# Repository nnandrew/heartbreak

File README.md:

# heartbreak
a 40 Key Wireless BLE Split Keyboard with Encoders, LCDs, Haptic Feedback, Fingerprint Reading, Underglow, and a corny theme.

## Parts
### Required

| Name | Count | Notes |
|:-|:-|:-|
| PCB | 2 | Reversible |
| PCB Coin | 1-2 | fills case hole with a <3 |
| Top Shell | 2  | 3D printed or machined integrated plate |
| Bottom Shell | 2  | Transparent resin print |
| Magnets | 48  | 3x1mm to hold the case together |
| nice!nano v2.0 | 2 | ZMK BLE |
| MCU Sockets | 50-70 | 0627-0-15-15-21-27-10-0 | 
| MCU Pins | 50-70 | 3320-0-00-15-00-00-03-0 |
| Reset Switch | 2 | B3U-3000P-B |
| Power Switch | 2 | PCM12 |
| Battery | 2 | 301230 size |
| Diodes | 42 | SOD-123 SMD |
| Switch Sockets | 40 | Kailh sockets |
| Key Switches | 40 | Only compatible with MX style |
| Keycaps | 40 | All 1u |
| USB C cable | 1 | Data lines required for flashing |

### Optional

| Name | Count | Remarks |
|:-|:-|:-|
| Rubber feet | 8 | reduce sliding |
| nice!view LCD | 2 | low power draw |
| Pimoroni Haptic Buzz | 1 | requires custom firmware |
| Waveshare UART Fingerprint Sensor | 1 | requires custom firmware |
| EC11 Rotary Encoder | 2 | using hardware debouncing |
| 17mm Encoder Knob | 2 | a tight fit |
| Schmitt Trigger | 2 | 74AUP2G14 |
| 10kOhm Resistors | 8 | encoder debounce |
| 0.1uC Capacitors | 4 | for leds and debounce |
| WS2812B | 9 | LEDs for Undergrow |
| SK6812-SIDE | 4 | LEDs for Undergrow |
| P-Channel MOSFET | 2 | SOT-23 to shutoff LEDs |
| 200Ohm Resistors | 2 | current limit for mosfet |
| 200kOhm Resistors | 2 | pulldown for mosfet |
| 0.1uC Capacitors | 26 | for leds and debounce |

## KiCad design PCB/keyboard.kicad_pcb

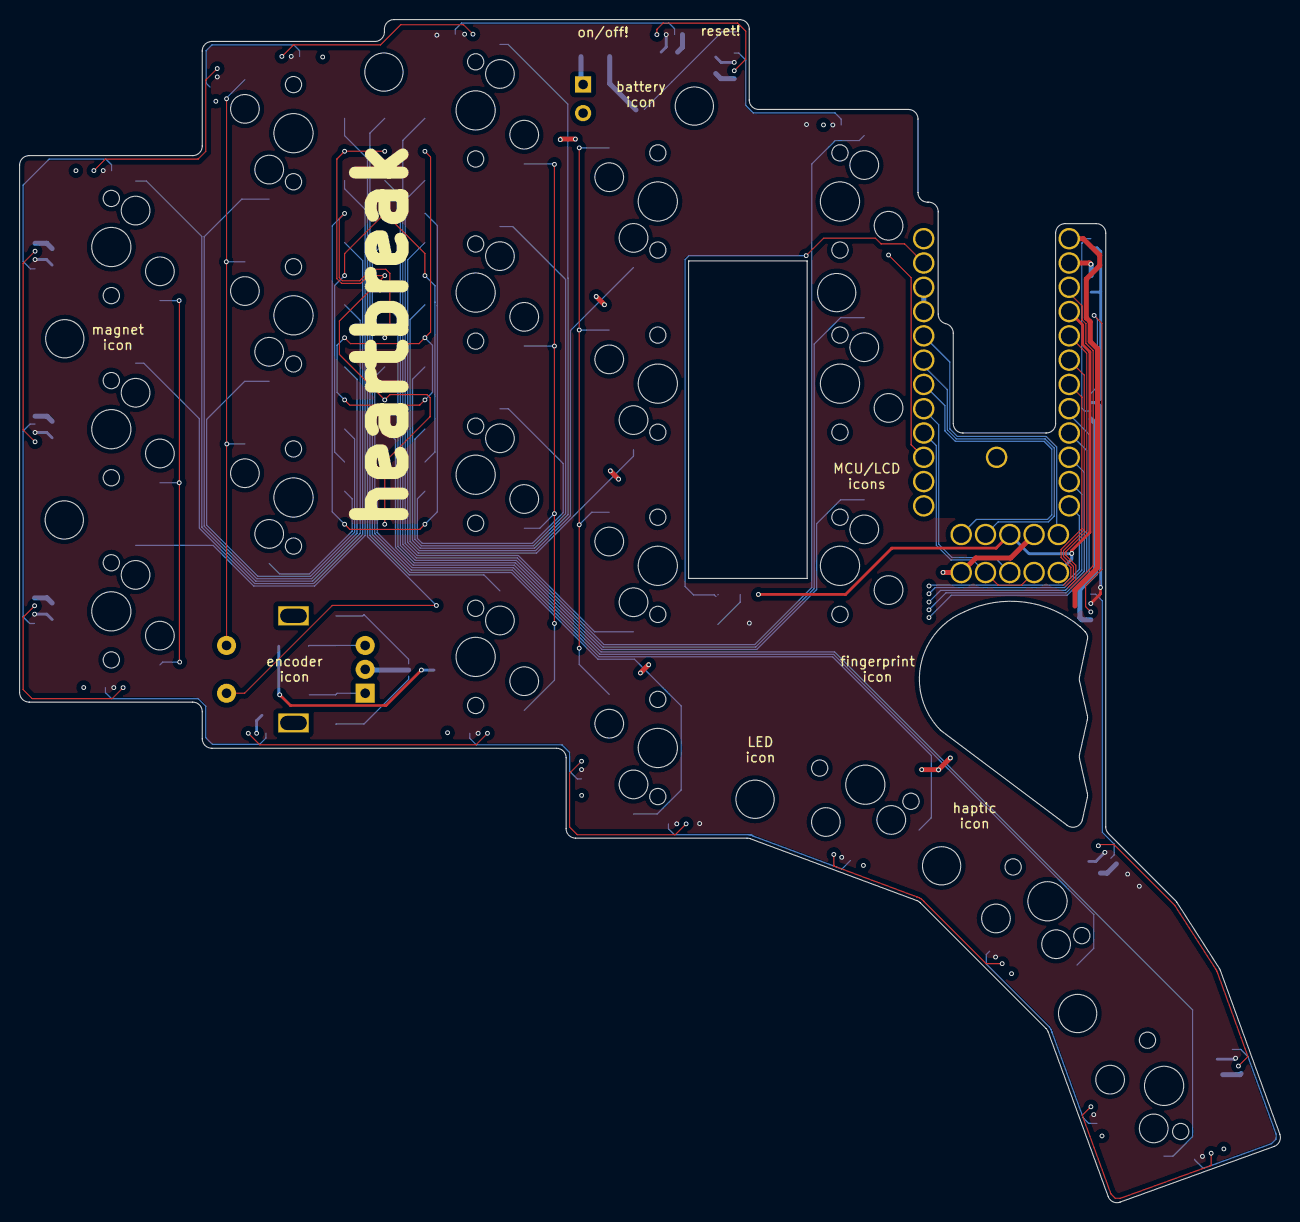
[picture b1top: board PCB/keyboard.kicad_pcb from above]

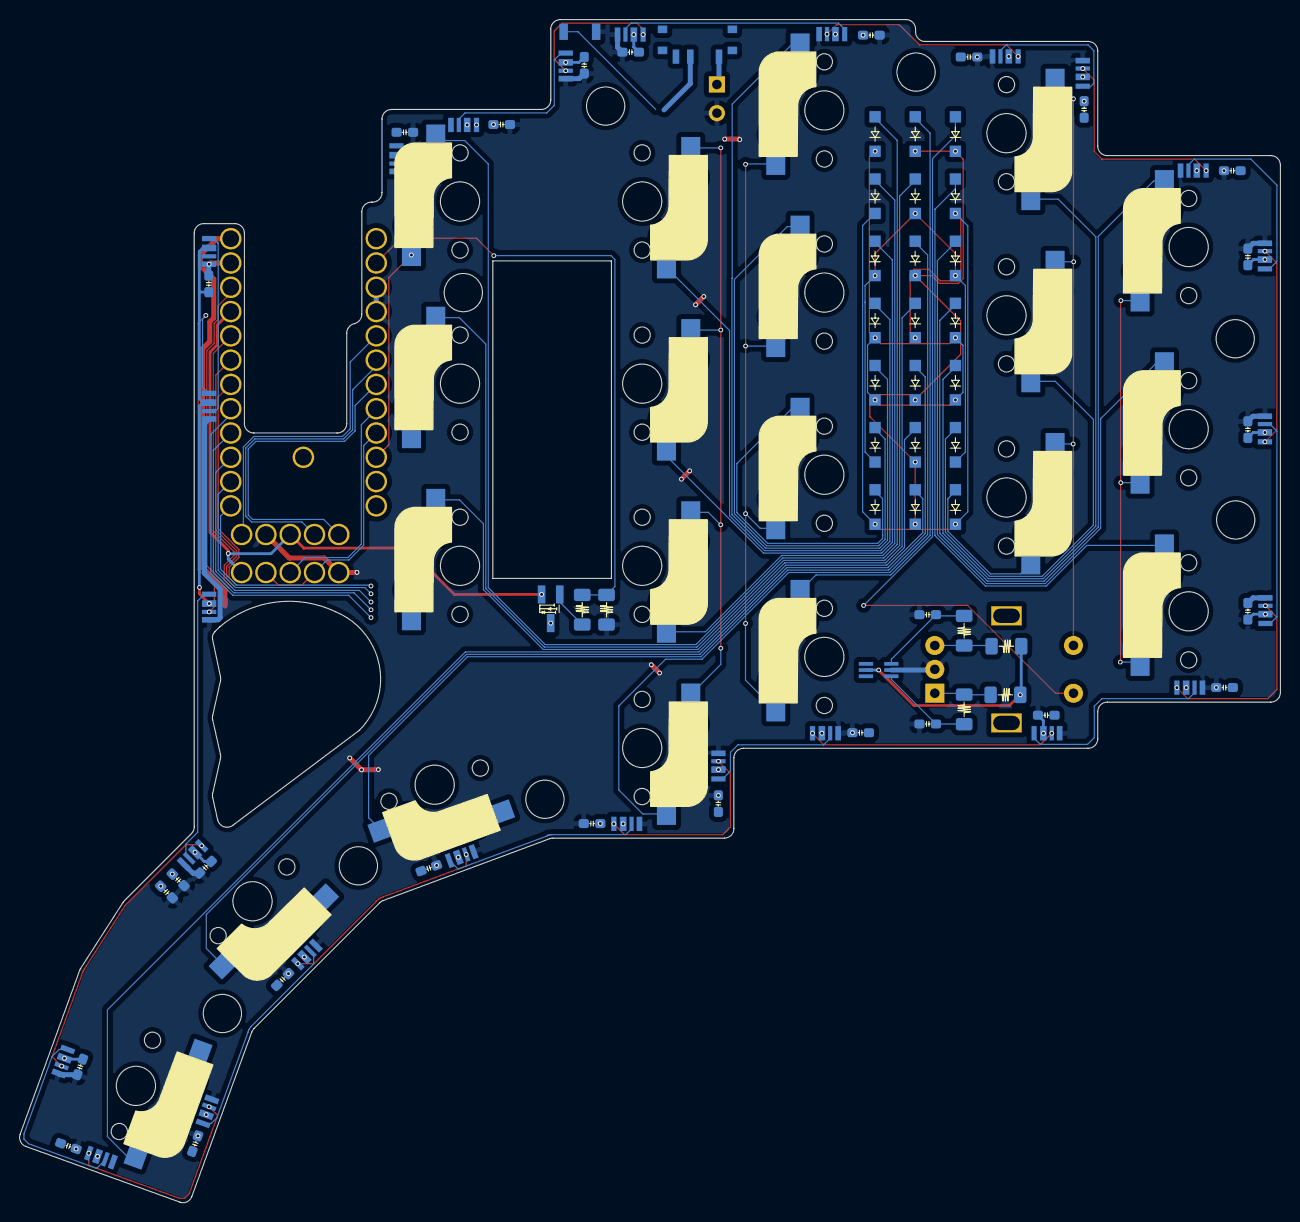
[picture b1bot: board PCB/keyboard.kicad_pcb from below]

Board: 2 copper layers, 131.8 x 123.7 mm, 116 parts (104 on the bottom side), 76 nets.

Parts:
C1, C2, C3, C4, C5, C6, C7, C8, C9, C10, C11, C12, C13, C14, C15, C16, C17, C18, C19, C20, C21, C22, C23, C24, C25, C26, C27: 0.1u; SMD_Cap_0603
D1, D2, D3, D4, D5, D6, D7, D8, D9, D10, D11, D12, D13, D14, D15, D16, D17, D18, D19, D20, D21: SMD_SOD123
H1, H2, H3, H4, H5, H6, H7, H8: MountingHole; MountingHole_4mm
J1: Conn_01x05; Pimoroni Haptic Buzz
J2: Conn_01x02; TH_BatteryConn
LCD1: nice!view
LED1, LED2, LED3, LED4, LED5, LED6, LED7, LED8, LED9, LED10, LED11, LED12, LED13, LED14, LED15, LED16, LED17, LED18, LED19, LED20, LED21, LED22, LED23, LED24, LED25: SK6812; SK6812-SIDE
Q1: Q_PMOS_GSD; SMD_P_MOSFET_SOT-23
R1, R2, R3, R4: 10k; SMD_Res_1206
R5: 200; SMD_Res_1206
R6: 200k; SMD_Res_1206
SW1, SW2, SW3, SW4, SW5, SW6, SW7, SW8, SW9, SW10, SW11, SW12, SW13, SW14, SW15, SW17, SW18, SW19, SW20, SW21: MX; SMD_CherryMX_MidHeight_HotSwap
SW16: RotaryEncoder_Switch; EC11
SW43: SW_DPDT_x2; SMD_SW_SPDT_PCM12
SW44: SW_PUSH; SMD_SW_SPST_B3U-3000P-B
U1: ProMicro_r; nice!nano
U2: 74AUP2G14; SMD_74AUP2G14_SOT-363

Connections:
+3V3: J1.1, LCD1.3 (VCC), Q1.2 (S), R1.1, R2.1, U1.21 (3.3V), U2.5 (VCC)
/RAW_BAT: J2.1, SW43.1 (A)
ARGB: LED1.1 (DIN), U1.1 (P0.06/H)
CS: LCD1.5 (CS), U1.5 (P0.17/H)
GND: C1.2, C2.2, C3.2, C4.2, C5.2, C6.1, C7.1, C8.1, C9.1, C10.1, C11.2, C12.2, C13.2, C14.2, C15.2, C16.1, C17.1, C18.1, C19.1, C20.1, C21.2, C22.2, C23.2, C24.2, C26.2, C27.2, J1.5, J2.2, LCD1.4 (GND), LED1.4 (VSS), LED2.4 (VSS), LED3.4 (VSS), LED4.4 (VSS), LED5.4 (VSS), LED6.4 (VSS), LED7.4 (VSS), LED8.4 (VSS), LED9.4 (VSS), LED10.4 (VSS), LED11.4 (VSS), LED12.4 (VSS), LED13.4 (VSS), LED14.4 (VSS), LED15.4 (VSS), LED16.4 (VSS), LED17.4 (VSS), LED18.4 (VSS), LED19.4 (VSS), LED20.4 (VSS), LED21.4 (VSS), LED22.4 (VSS), LED23.4 (VSS), LED24.4 (VSS), R6.2, SW16.C, SW44.2, U1.3 (GND), U1.4 (GND), U2.2 (GND)
GND1: C25.2, LED25.4 (VSS), U1.23 (GND)
LED: R5.1, R6.1, U1.2 (P0.08/H)
LED_VCC: C1.1, C2.1, C3.1, C4.1, C5.1, C6.2, C7.2, C8.2, C9.2, C10.2, C11.1, C12.1, C13.1, C14.1, C15.1, C16.2, C17.2, C18.2, C19.2, C20.2, C21.1, C22.1, C23.1, C24.1, C25.1, LED1.2 (VDD), LED2.2 (VDD), LED3.2 (VDD), LED4.2 (VDD), LED5.2 (VDD), LED6.2 (VDD), LED7.2 (VDD), LED8.2 (VDD), LED9.2 (VDD), LED10.2 (VDD), LED11.2 (VDD), LED12.2 (VDD), LED13.2 (VDD), LED14.2 (VDD), LED15.2 (VDD), LED16.2 (VDD), LED17.2 (VDD), LED18.2 (VDD), LED19.2 (VDD), LED20.2 (VDD), LED21.2 (VDD), LED22.2 (VDD), LED23.2 (VDD), LED24.2 (VDD), LED25.2 (VDD), Q1.3 (D)
MOSI: LCD1.1 (MOSI), U1.7 (P0.22/H)
unnamed: R3.2, U2.1
unnamed: R4.2, U2.3
unnamed: D1.2 (A), SW1.2 (ROW)
unnamed: D2.2 (A), SW2.2 (ROW)
unnamed: D3.2 (A), SW3.2 (ROW)
unnamed: D4.2 (A), SW4.2 (ROW)
unnamed: D5.2 (A), SW5.2 (ROW)
unnamed: D6.2 (A), SW6.2 (ROW)
unnamed: D7.2 (A), SW7.2 (ROW)
unnamed: D8.2 (A), SW8.2 (ROW)
unnamed: D9.2 (A), SW9.2 (ROW)
unnamed: D10.2 (A), SW10.2 (ROW)
unnamed: D11.2 (A), SW11.2 (ROW)
unnamed: D12.2 (A), SW12.2 (ROW)
unnamed: D13.2 (A), SW13.2 (ROW)
unnamed: D14.2 (A), SW14.2 (ROW)
unnamed: D15.2 (A), SW15.2 (ROW)
unnamed: D17.2 (A), SW17.2 (ROW)
unnamed: D18.2 (A), SW18.2 (ROW)
unnamed: D19.2 (A), SW19.2 (ROW)
unnamed: D20.2 (A), SW20.2 (ROW)
unnamed: D21.2 (A), SW21.2 (ROW)
unnamed: LED1.3 (DOUT), LED2.1 (DIN)
unnamed: LED2.3 (DOUT), LED3.1 (DIN)
unnamed: LED3.3 (DOUT), LED4.1 (DIN)
unnamed: LED4.3 (DOUT), LED5.1 (DIN)
unnamed: LED5.3 (DOUT), LED6.1 (DIN)
unnamed: LED6.3 (DOUT), LED7.1 (DIN)
unnamed: LED7.3 (DOUT), LED8.1 (DIN)
unnamed: LED8.3 (DOUT), LED9.1 (DIN)
unnamed: LED9.3 (DOUT), LED10.1 (DIN)
unnamed: LED10.3 (DOUT), LED11.1 (DIN)
unnamed: LED11.3 (DOUT), LED12.1 (DIN)
unnamed: LED12.3 (DOUT), LED13.1 (DIN)
unnamed: LED13.3 (DOUT), LED14.1 (DIN)
unnamed: LED14.3 (DOUT), LED15.1 (DIN)
unnamed: LED16.3 (DOUT), LED17.1 (DIN)
unnamed: LED17.3 (DOUT), LED18.1 (DIN)
unnamed: LED18.3 (DOUT), LED19.1 (DIN)
unnamed: LED19.3 (DOUT), LED20.1 (DIN)
unnamed: LED20.3 (DOUT), LED21.1 (DIN)
unnamed: LED21.3 (DOUT), LED22.1 (DIN)
unnamed: LED22.3 (DOUT), LED23.1 (DIN)
unnamed: LED23.3 (DOUT), LED24.1 (DIN)
unnamed: LED24.3 (DOUT), LED25.1 (DIN)
unnamed: Q1.1 (G), R5.2
unnamed: R1.2, R3.1, SW16.A
unnamed: R2.2, R4.1, SW16.B
RAW: SW43.2 (B), U1.24 (BAT+)
RESET: SW44.1, U1.22 (RESET)
R_LED_VCC: C26.1, C27.1
SCK: LCD1.2 (SCK), U1.6 (P0.20/H)
SCL/RX: J1.3, U1.8 (P0.24/H)
SDA/TX: J1.2, J1.4, U1.9 (P1.00/H)
col0: SW1.1 (COL), SW6.1 (COL), SW11.1 (COL), SW21.1 (COL), U1.16 (P1.13/L)
col1: SW2.1 (COL), SW7.1 (COL), SW12.1 (COL), SW16.S1, U1.15 (P1.11/L)
col2: SW3.1 (COL), SW8.1 (COL), SW13.1 (COL), SW17.1 (COL), U1.14 (P0.10/L)
col3: SW4.1 (COL), SW9.1 (COL), SW14.1 (COL), SW18.1 (COL), U1.13 (P0.09/L)
col4: SW5.1 (COL), SW10.1 (COL), SW15.1 (COL), SW19.1 (COL), U1.10 (P0.11/H)
col5: SW20.1 (COL), U1.27 (P1.07/L)
rotA: U1.12 (P1.06/L), U2.6
rotB: U1.11 (P1.04/L), U2.4
rotS2: D16.2 (A), SW16.S2
row0: D1.1 (K), D2.1 (K), D3.1 (K), D4.1 (K), D5.1 (K), U1.20 (P0.31/L)
row1: D6.1 (K), D7.1 (K), D8.1 (K), D9.1 (K), D10.1 (K), U1.19 (P0.29/L)
row2: D11.1 (K), D12.1 (K), D13.1 (K), D14.1 (K), D15.1 (K), U1.18 (P0.02/L)
row3: D16.1 (K), D17.1 (K), D18.1 (K), D19.1 (K), D20.1 (K), D21.1 (K), U1.17 (P1.15/L)

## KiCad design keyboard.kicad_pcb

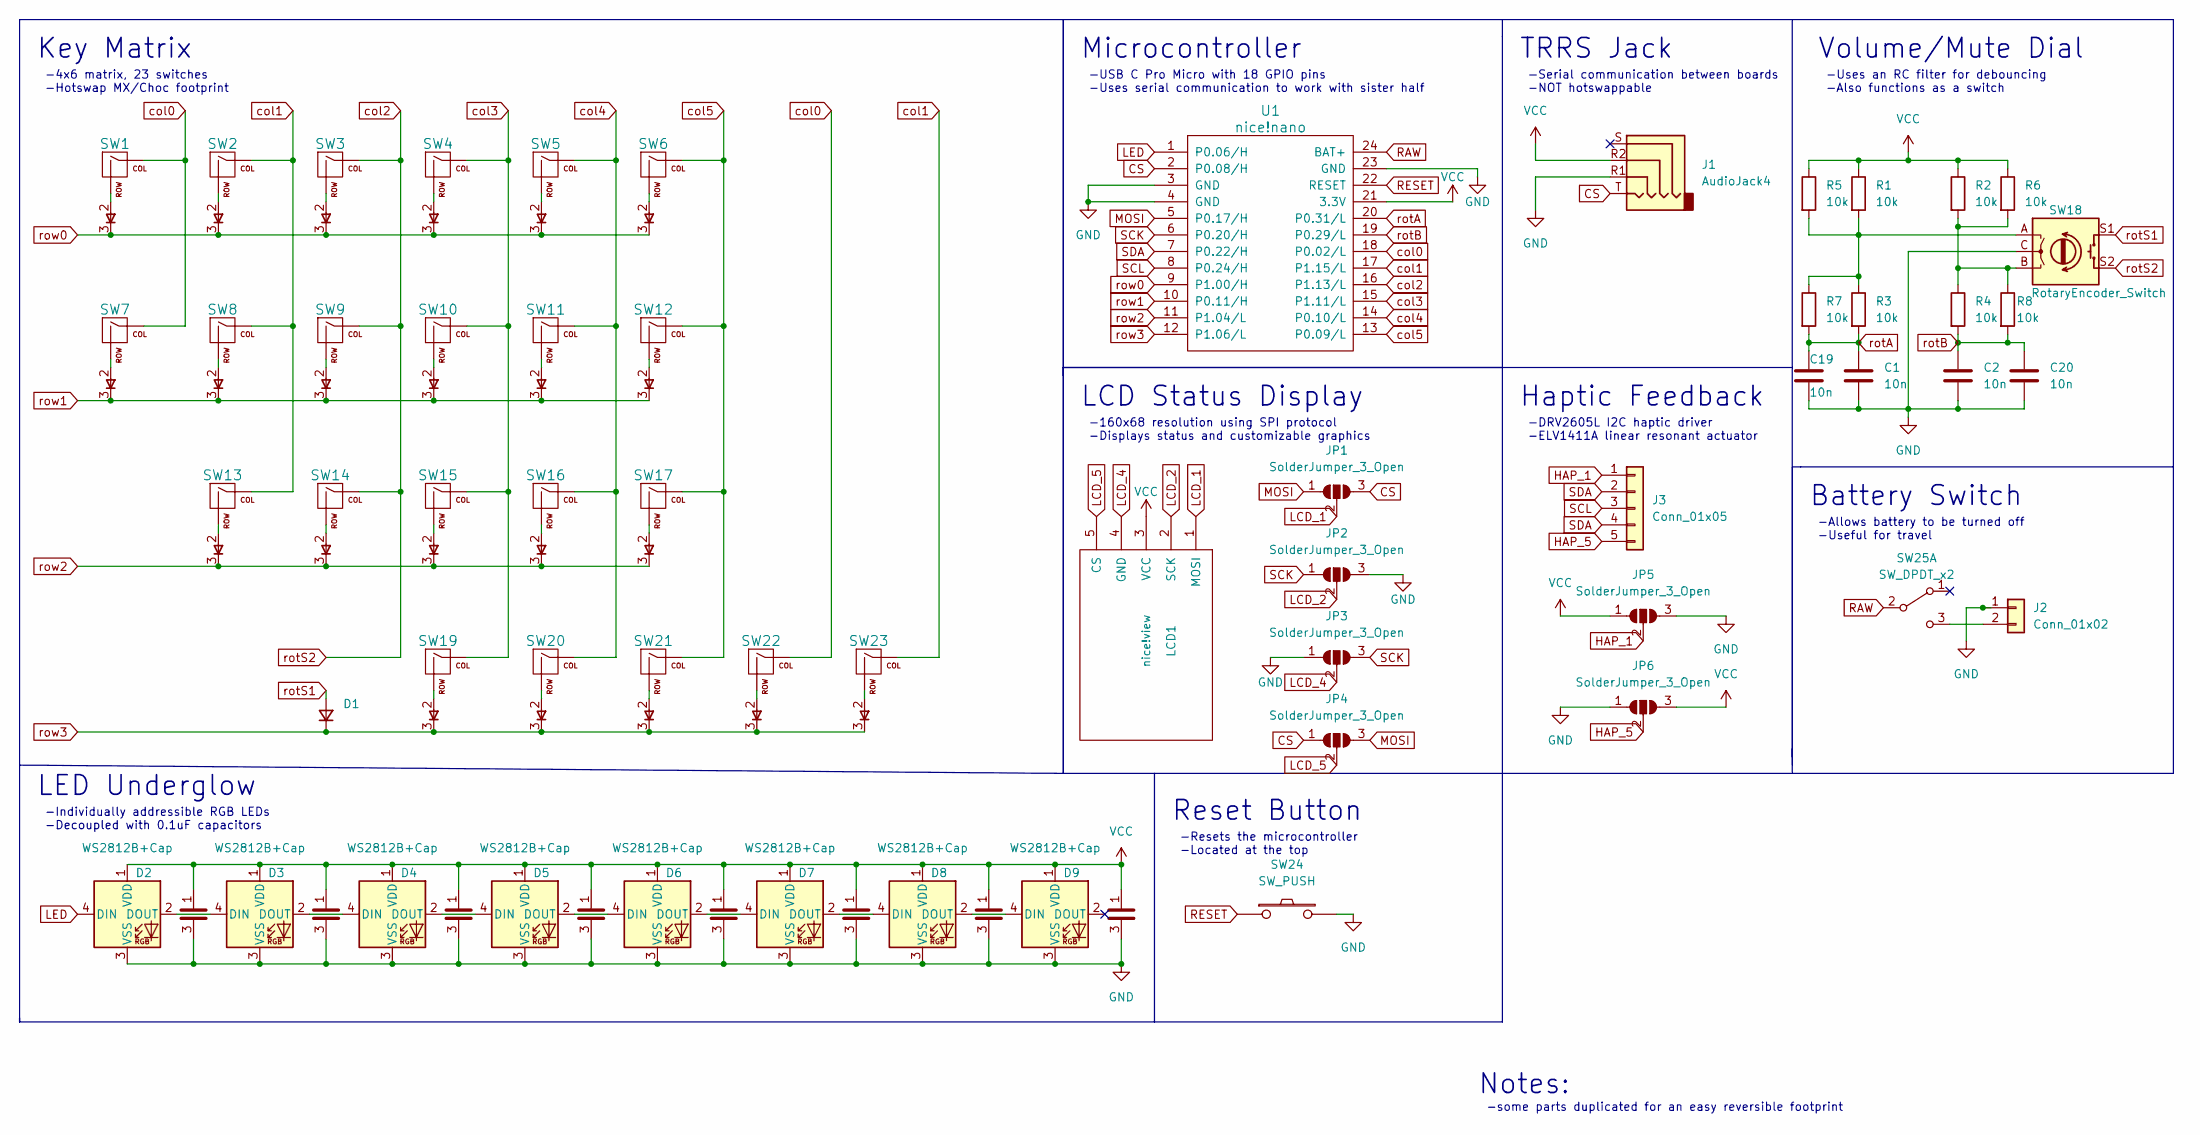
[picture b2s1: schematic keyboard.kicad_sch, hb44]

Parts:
C1, C2, C19, C20: 10n; Cap_0603_Clean
D1: SMD_SOD123
D2, D3, D4, D5, D6, D7, D8, D9: WS2812B+Cap; SMD_WS2812B+Cap0603
J1: AudioJack4; SMD_3.5mm_TRRS
J2: Conn_01x02; TH_BatteryConn
J3: Conn_01x05; Pimoroni Haptic Buzz DRV2605L Driver
JP1, JP2, JP3, JP4, JP5, JP6: SolderJumper_3_Open; jumperClean
LCD1: nice!view
R1, R2, R3, R4, R5, R6, R7, R8: 10k; Res_1206_Clean
SW1, SW2, SW3, SW4, SW5, SW6, SW7, SW8, SW9, SW10, SW11, SW12, SW13, SW14, SW15, SW16, SW17, SW19, SW20, SW21, SW22, SW23: Switch+Diode; SMD_CherryMX_MidHeight_Choc_HotSwap+SOD123
SW18: RotaryEncoder_Switch; ec11
SW24: SW_PUSH; SMD_SW_PUSH
SW25: SW_DPDT_x2; SW_SPDT_PCM12
U1: nice!nano

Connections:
CS: J1.T, JP1.3 (B), JP4.1 (A), U1.2 (P0.08/H)
GND: C1.2, C2.2, C19.2, C20.2, D2.3 (VSS), D3.3 (VSS), D4.3 (VSS), D5.3 (VSS), D6.3 (VSS), D7.3 (VSS), D8.3 (VSS), D9.3 (VSS), J1.R1, J2.1, JP2.3 (B), JP3.1 (A), JP5.3 (B), JP6.1 (A), SW18.C, SW24.2, U1.3 (GND), U1.4 (GND), U1.23 (GND)
HAP_1: J3.1, JP5.2 (C)
HAP_5: J3.5, JP6.2 (C)
LCD_1: JP1.2 (C), LCD1.1 (MOSI)
LCD_2: JP2.2 (C), LCD1.2 (SCK)
LCD_4: JP3.2 (C), LCD1.4 (GND)
LCD_5: JP4.2 (C), LCD1.5 (CS)
LED: D2.4 (DIN), U1.1 (P0.06/H)
MOSI: JP1.1 (A), JP4.3 (B), U1.5 (P0.17/H)
unnamed: D2.2 (DOUT), D3.4 (DIN)
unnamed: D3.2 (DOUT), D4.4 (DIN)
unnamed: D4.2 (DOUT), D5.4 (DIN)
unnamed: D5.2 (DOUT), D6.4 (DIN)
unnamed: D6.2 (DOUT), D7.4 (DIN)
unnamed: D7.2 (DOUT), D8.4 (DIN)
unnamed: D8.2 (DOUT), D9.4 (DIN)
unnamed: J2.2, SW25.3 (C)
unnamed: R1.2, R3.1, R5.2, R7.1, SW18.A
unnamed: R2.2, R4.1, R6.2, R8.1, SW18.B
RAW: SW25.2 (B), U1.24 (BAT+)
RESET: SW24.1, U1.22 (RESET)
SCK: JP2.1 (A), JP3.3 (B), U1.6 (P0.20/H)
SCL: J3.3, U1.8 (P0.24/H)
SDA: J3.2, J3.4, U1.7 (P0.22/H)
VCC: D2.1 (VDD), D3.1 (VDD), D4.1 (VDD), D5.1 (VDD), D6.1 (VDD), D7.1 (VDD), D8.1 (VDD), D9.1 (VDD), J1.R2, JP5.1 (A), JP6.3 (B), LCD1.3 (VCC), R1.1, R2.1, R5.1, R6.1, U1.21 (3.3V)
col0: SW1.1 (COL), SW7.1 (COL), SW22.1 (COL), U1.18 (P0.02/L)
col1: SW2.1 (COL), SW8.1 (COL), SW13.1 (COL), SW23.1 (COL), U1.17 (P1.15/L)
col2: SW3.1 (COL), SW9.1 (COL), SW14.1 (COL), SW18.S2, U1.16 (P1.13/L)
col3: SW4.1 (COL), SW10.1 (COL), SW15.1 (COL), SW19.1 (COL), U1.15 (P1.11/L)
col4: SW5.1 (COL), SW11.1 (COL), SW16.1 (COL), SW20.1 (COL), U1.14 (P0.10/L)
col5: SW6.1 (COL), SW12.1 (COL), SW17.1 (COL), SW21.1 (COL), U1.13 (P0.09/L)
rotA: C1.1, C19.1, R3.2, R7.2, U1.20 (P0.31/L)
rotB: C2.1, C20.1, R4.2, R8.2, U1.19 (P0.29/L)
rotS1: D1.2 (A), SW18.S1
row0: SW1.3, SW2.3, SW3.3, SW4.3, SW5.3, SW6.3, U1.9 (P1.00/H)
row1: SW7.3, SW8.3, SW9.3, SW10.3, SW11.3, SW12.3, U1.10 (P0.11/H)
row2: SW13.3, SW14.3, SW15.3, SW16.3, SW17.3, U1.11 (P1.04/L)
row3: D1.1 (K), SW19.3, SW20.3, SW21.3, SW22.3, SW23.3, U1.12 (P1.06/L)

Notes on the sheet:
-Serial communication between boards -NOT hotswappable
-4x6 matrix, 23 switches -Hotswap MX/Choc footprint
Reset Button
-USB C Pro Micro with 18 GPIO pins -Uses serial communication to work with sister half
-Allows battery to be turned off -Useful for travel
Key Matrix
Microcontroller
-DRV2605L I2C haptic driver -ELV1411A linear resonant actuator
-Resets the microcontroller -Located at the top
LCD Status Display
-Uses an RC filter for debouncing -Also functions as a switch
TRRS Jack
LED Underglow
Notes:
Battery Switch
-some parts duplicated for an easy reversible footprint
-Individually addressible RGB LEDs -Decoupled with 0.1uF capacitors
-160x68 resolution using SPI protocol -Displays status and customizable graphics
Haptic Feedback
Volume/Mute Dial

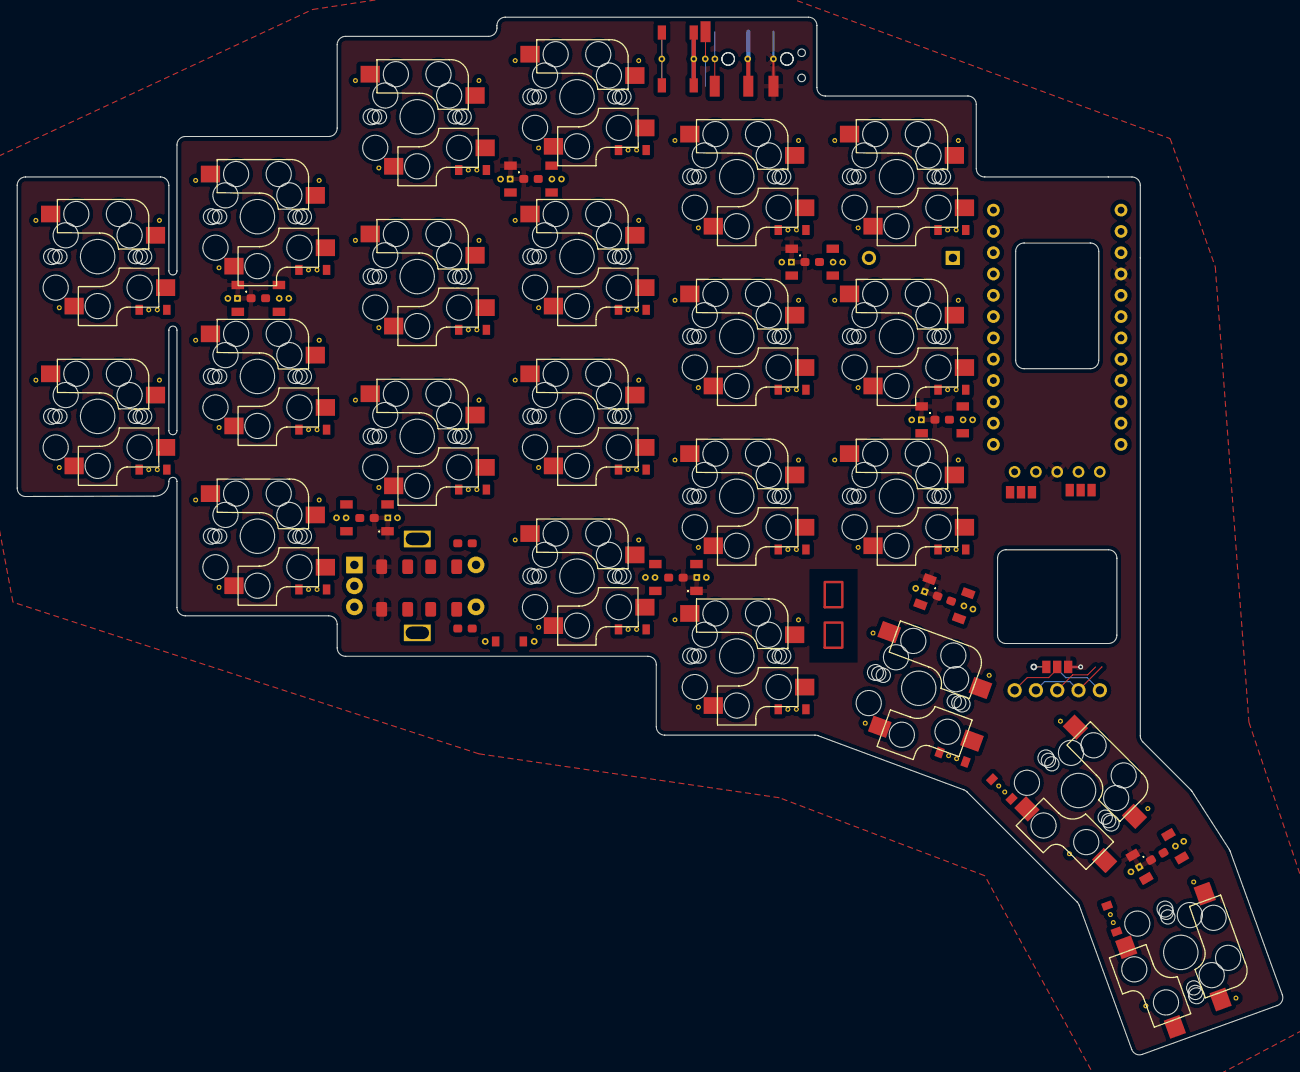
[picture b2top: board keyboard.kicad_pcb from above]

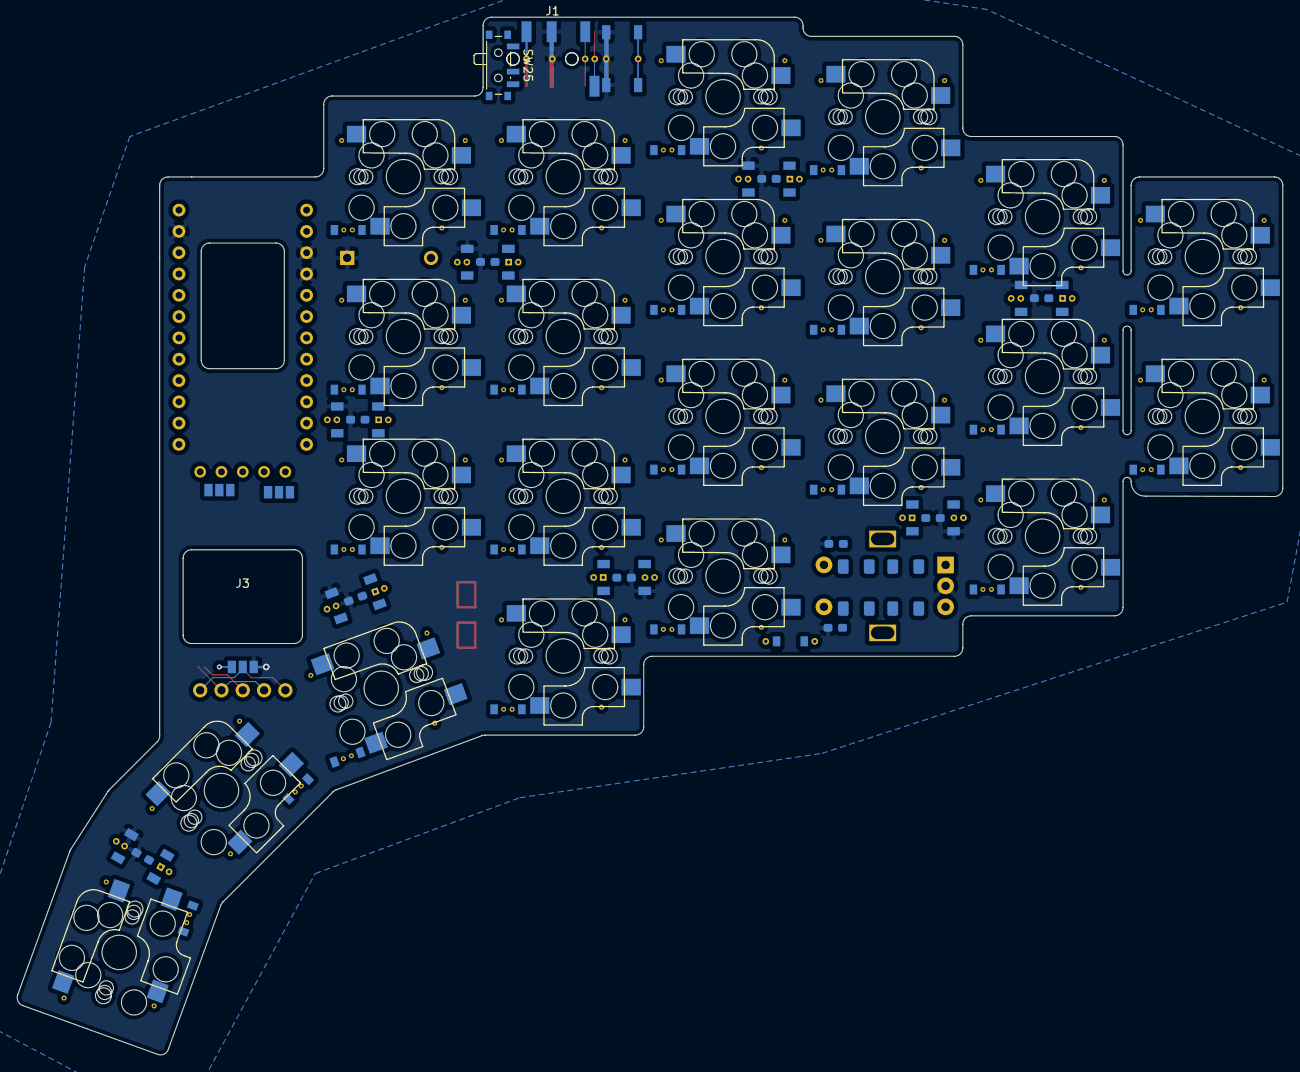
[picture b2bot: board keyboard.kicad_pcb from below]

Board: 2 copper layers, 150.9 x 123.7 mm, 57 parts (23 on the bottom side), 39 nets.

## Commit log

2022-09-06 Update README.md
    added images
2022-09-13 added more renders
2022-10-02 wireless
2022-10-02 folder structure
2022-10-05 preliminary routing
2022-10-10 3d assets + bad routing
2022-10-10 more renders
2022-10-14 wired compatible/breakaway
2022-10-16 curvy traces
2022-10-16 housekeeping
    deleted unused files
2022-10-28 working 44
2022-11-28 reversible WIP
2022-12-04 vertical
2022-12-27 production
2024-05-07 cleaned directory + led fix
